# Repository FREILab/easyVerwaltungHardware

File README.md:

# easyVerwaltung Hardware

Firmware und Dokumentation für die **easyVerwaltung**-Hardware des FREILab. Das System steuert Maschinenzugang, Nutzungsprotokollierung und Sicherheit via RFID-Authentifizierung gegen das easyVerwaltung-Backend.

---

## Hardware-Übersicht

### RFID-Box — Maschinenfreigabe

| Projekt | Hardware | API | Status |
|---|---|---|---|
| [RFID_BOX_legacy](firmware/projects/RFID_BOX_legacy/) | ESP32 Dev1 | Legacy | Stabil — [v1.0.0](https://github.com/FREILab/easyVerwaltungHardware/releases/tag/rfid-box-legacy%2Fv1.0.0) |
| [RFID_BOX_easyVerwaltung](firmware/projects/RFID_BOX_easyVerwaltung/) | ESP32 Dev1 | easyVerwaltung | Getestet — Server noch nicht in Production |

### Tür-Steuerung

| Projekt | Hardware | API | Status |
|---|---|---|---|
| [DOOR_legacy](firmware/projects/DOOR_legacy/) | Arduino UNO R4 WiFi | Legacy | Scheduled for Deletion |
| [DOOR_legacy_ESPArdu](firmware/projects/DOOR_legacy_ESPArdu/) | RobotDyn UNO+WiFi R3 (ATmega328P + ESP8266) | Legacy | Stabil — [v1.0.0](https://github.com/FREILab/easyVerwaltungHardware/releases/tag/door-legacy-espardu%2Fv1.0.0) |
| [DOOR_easyVerwaltung](firmware/projects/DOOR_easyVerwaltung/) | Arduino UNO R4 WiFi | easyVerwaltung | In Entwicklung |

### Lasersaur HMI

| Projekt | Hardware | API | Status |
|---|---|---|---|
| [LASERSAUR_HMI_legacy](firmware/projects/LASERSAUR_HMI_legacy/) | Arduino Mega + Ethernet-Shield | Legacy | Stabil (nicht mit neuem Server getestet) — wird durch ESPArdu ersetzt |
| [LASERSAUR_HMI_ESPArdu](firmware/projects/LASERSAUR_HMI_ESPArdu/) | Mega2560 WiFi R3 (ATmega2560 + ESP8266) | Legacy | Implementiert, noch nicht getestet |
| [LASERSAUR_HMI_easyVerwaltung](firmware/projects/LASERSAUR_HMI_easyVerwaltung/) | Arduino Giga R1 | easyVerwaltung | In Entwicklung |

### Machine Node

| Projekt | Hardware | API | Status |
|---|---|---|---|
| [MachineNode_legacy](firmware/projects/MachineNode_legacy/) | ESP32-S3-WROOM-1-N16R8 | Legacy | Stabil |
| [MachineNode_easyVerwaltung](firmware/projects/MachineNode_easyVerwaltung/) | ESP32-S3-WROOM-1-N16R8 | easyVerwaltung | Geplant |

---

## Repository-Struktur

```
firmware/
  projects/          # Firmware-Targets (je ein PlatformIO-Projekt)
  shared/
    easyAPI/         # Gemeinsame Backend-Kommunikation (HTTP/JSON)
```

Jedes Projekt in `projects/` enthält eine eigene `README.md` mit Hardware-Details, DIP-Belegung, Flash-Anleitung und Debugging-Hinweisen.

---

## Einrichtung

### Voraussetzungen

- Python ≥ 3.8
- PlatformIO Core (`pip install platformio`)

### Credentials

Jedes Projekt benötigt eine `platformio.secrets.ini` (nicht in Git). Vorlage liegt als `.example`-Datei bei:

```bash
cp platformio.secrets.ini.example platformio.secrets.ini
# Datei befüllen, dann:
pio run
```

Details zu den Feldern stehen in der jeweiligen Projekt-README.

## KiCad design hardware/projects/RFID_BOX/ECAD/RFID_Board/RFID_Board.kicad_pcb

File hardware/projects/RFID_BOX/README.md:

# Machine Node / RFID_BOX

> **Sicherheit geht vor Kosten, Baugröße und Bauteilzahl.** Das Gerät
> schaltet Netzspannung in einer Werkstatt, in der ungeschulte Personen
> daneben stehen. Wo Ziele kollidieren, gewinnt die Sicherheit.
>
> Vier Festlegungen sind bindend und werden nicht aufgeweicht:
>
> - Die Barriere Netz ↔ SELV beträgt **8 mm Luft- und Kriechstrecke** und
>   wird nicht auf den Normwert von 5 mm reduziert. Maßgeblich sind die
>   Bauteile, die sie queren, nicht das Minimum der Norm.
> - Bauteile über der Barriere brauchen **verstärkte oder doppelte
>   Isolierung** bei 250 V Arbeitsspannung. Eine hohe Prüfspannung in kV
>   allein genügt nicht — sie sagt über die Isolationsklasse nichts aus.
> - **Ein Einzelfehler darf nicht nach außen wirken.** Neue Schaltungsteile
>   werden gegen die [FMEA](FMEA.md) geprüft, bevor sie ins Layout gehen.
> - **Beim geöffneten Gerät ist nichts Netzführendes berührbar.** Feste
>   Abdeckplatten über dem I/O-Board geben nur die Feldterminals und den
>   Sicherungshalter frei. Das RFID-Board führt kein 230 V und darf
>   angefasst werden.
>
> Breiten, Abstände und Domänen stehen in
> [Layoutregeln.md](Layoutregeln.md), die Anforderungen in
> [Anforderungen.md](Anforderungen.md). Wo das Gerät teuer ist und was eine
> Alternative kosten würde, führt [Kostenoptimierung.md](Kostenoptimierung.md)
> mit — keine der Positionen dort hebt eine der vier Festlegungen auf.

## Einleitung

Dies ist der **RFID Node**: ein kompaktes Steuergerät, das elektrische
Geräte und Maschinen in der Werkstatt (z.B. Standfräse, Drehmaschine, FKS)
per RFID-Karte freischaltet. Er prüft die Karte einer Nutzerin oder eines
Nutzers gegen easyVerwaltung, gibt bei gültiger Berechtigung die Maschine
frei und schaltet sie beim Stopp oder bei Kartenentzug wieder ab.

Technisch besteht der Node aus zwei Platinen — I/O-Board mit Netzteil und
Schaltausgang, RFID-Board mit Controller, Bedienoberfläche und
RFID-Frontend — ergänzt um optionale Erweiterungsboards für Maschinen mit
zusätzlichem Bedarf.

## Aufbau

Das Gehäuse ist 3D-gedruckt und staubdicht ausgeführt. Display und
LED-Streifen sind von aussen sichtbar und durch eine Plexiglasscheibe
geschützt; der Streifen selbst sitzt innerhalb des Gehäuses. Der Stopp-Knopf
ist von aussen erreichbar.

Das Display sitzt nicht auf der Platine, sondern in einem eigenen
3D-gedruckten Träger, der von innen hinter die Plexiglasscheibe geklippt
wird. Die Verbindung zum RFID-Board läuft über das FPC des Displays.

Die Mechanik — Gehäuse, Display-Träger, Abdeckplatten — lebt in Fusion, nicht
in diesem Repo. Von dort kommen auch die Platinenumrisse als DXF
(`PCB_outline/`).

Die beiden Platinen sitzen in verschiedenen Gehäusehälften: das
**RFID-Board am Deckel**, das **I/O-Board an der unteren Schale**. Verbunden
werden sie über ein **Kabel** — für einen Board-to-Board-Stecker ist der
Abstand zu groß. Der Deckel hängt beim Öffnen damit am Kabel.

Alle Kabel werden einseitig über Kabeldurchführungen ins Gehäuse geführt,
von links nach rechts: Netz-Eingang 230 V, Schaltausgang (geschaltete 230 V
oder Steuerleitung für ein externes Schütz), optionale Notaus-Schleife,
optionales Extension-I/O. Nicht verwendete Durchführungen werden
verschlossen.

### Berührschutz

Das Gerät wird im Servicefall geöffnet, während es unter Umständen noch am
Netz hängt. Deshalb:

- Über dem I/O-Board sitzen **fest installierte, 3D-gedruckte
  Abdeckplatten**. Sie geben nur die Feldterminals und den Sicherungshalter
  frei — beide sind berührsichere Bauformen (WAGO Hebelklemme, WR-FSH mit
  Shocksafe PC2/IP20). Alles andere Netzführende bleibt abgedeckt.
- Die Platten sind kein Deckel, der beim Öffnen mitkommt: sie bleiben am
  Board bzw. am Gehäuseunterteil und lassen sich nur mit Werkzeug lösen.
- **Das RFID-Board führt kein 230 V** und darf im geöffneten Zustand
  berührt werden. Das ist eine bindende Randbedingung — es darf kein
  netzführendes Netz auf dieses Board wandern.

Alle Boards werden **lackiert**, damit Sägemehl und Feuchtigkeit über die
Lebensdauer keine Kriechpfade bilden. Vom Lack ausgenommen bleiben
Feldterminals, Sicherungskontakte und die Steckverbinder. Der Lack
ersetzt keine Abstände: Kriech- und Luftstrecken werden bemessen, als wäre
kein Lack vorhanden.

## Elektronik

Zwei Leiterplatten, in verschiedenen Gehäusehälften:

- **RFID-Board (im Deckel):** ESP32-S3, NFC-Controller CLRC663 mit der
  RFID-Antenne, Display, LED-Streifen, Buzzer, Stopp-Taster und eine
  USB-C-Buchse für Erstprogrammierung und Debug. MCU- und RFID-Teil lagen früher getrennt
  und sind zusammengelegt.
- **I/O-Board (in der unteren Schale):** 230-V-Netz, Schaltausgang und die
  Extension-Header.
  Hiervon gibt es **zwei getrennte Boards mit eigenem Layout**, von denen
  pro Gerät genau eines bestückt wird:
  - **I/O-Board 230V** — Lastrelais und Lastmessung zum direkten Schalten
    von Lasten bis 8 A.
  - **I/O-Board 24V** — potentialfreier Kontakt für ein externes Schütz.
    Ohne Lastpfad und Lastmessung, dadurch deutlich einfacher und ohne
    Bedarf an 70 µm Kupfer.

  Beide haben denselben Formfaktor und denselben Kabelstecker zum
  RFID-Board.

Dazu kommen zwei optionale, steckbare Erweiterungsboards auf dem I/O-Board:

- **Extension Board:** generisches Zusatzboard mit zwei Bestückvarianten —
  **NAMUR** (zwei optoisolierte Ausgänge, ein galvanisch getrennter Eingang)
  oder **Digital-I/O** (noch nicht spezifiziert). Ein Node trägt höchstens
  eine Variante.
- **E-Stop Extension Board:** Relais (24 V / 100 mA), dessen Kontakt in die
  Notaus-/Interlock-Schleife oder Bremsversorgung der Maschine eingeschleift
  wird. Fail-safe: stromlos = Schleife unterbrochen. Es öffnet bei Stopp
  oder Kartenentzug sofort, während die Hauptversorgung erst nach der
  Nachlaufzeit trennt.

## Energieversorgung

Die gesamte Versorgung kommt aus dem Netz-Eingang 230 V auf dem I/O-Board
und teilt sich dort in zwei Pfade:

- **Lastpfad (nur I/O-Board 230V):** Netz-Eingang → Ausgangssicherung (F300)
  → Lastrelais (K300) → Schaltausgang. Der Shunt (R307) liegt im
  **N-Rückweg vor dem Relais**, damit die Messung unabhängig vom
  Schaltzustand betriebsbereit bleibt. K300 trennt L und N gemeinsam, weil
  die N/L-Zuordnung an der Werkstatt-Steckdose nicht garantiert eindeutig
  ist.
- **Steuerpfad:** Netz-Eingang → Sicherung F302 → Gleichtaktdrossel (L300) →
  Y-Kondensatorpaar (C305/C308, Mittelabgriff an PE) → isoliertes
  AC/DC-Modul (U300, 24 V) → Regler auf 5 V (U302). Über das Kabel geht nur
  die 5-V-Schiene zum RFID-Board; **die 3,3 V erzeugt jede Platine selbst** —
  IC304 auf dem I/O-Board für die Eingangsseite des Isolators, IC102 auf dem
  MCU-Board für ESP32, NFC-Frontend und Display. Der DC-DC im Isolator zieht
  seinen Strom damit lokal und nicht über 30 cm Kabel. Die 24-V-Schiene
  versorgt die Relaisspule und bleibt auf dem I/O-Board; zum MCU-Board geht
  statt der Schiene nur ein Teilersignal zur Überwachung. LED-Leiste und
  Buzzer laufen direkt auf 5 V.
- **USB-C:** Das RFID-Board lässt sich auch allein über USB versorgen. VBUS
  (D401) und die 5 V vom Kabel (D100) laufen über je eine Schottky-Diode SS14
  auf +5V; keine Quelle speist in die andere zurück. Die Schiene liegt damit
  rund 0,4 V unter 5 V — für den 74AHCT125 (min. 4,5 V) knapp ausreichend.

Die **Lastmessung** liegt auf Netzpotential. Versorgung und UART laufen über
den Digitalisolator U301 (ISOW7721) mit integriertem DC-DC-Wandler, gespeist
aus der SELV-Seite — die Insel führt keinen eigenen Netzzweig. Über `ISO_EN`
nimmt die Firmware der Insel die Versorgung und startet das Mess-IC U303 neu.

Die Erweiterungsboards stecken auf dem I/O-Board und werden aus dem
Steuerpfad versorgt;
ihre Feldseite bleibt galvanisch getrennt und wird extern gespeist.

PE wird unverändert vom Netz-Eingang zum Schaltausgang durchgeschleift und
trägt den Mittelabgriff von C305/C308. Das Gehäuse ist Kunststoff, es gibt
keine Gehäusemasse.

**Sicherungen.** Die Lastausgangssicherung (F300) ist gesockelt und nach dem
Öffnen des Gehäuses ohne Löten tauschbar; eine Ersatzsicherung wird im
Gehäuse mitgeführt. Die Gerätesicherung (F302) ist als dokumentierte
Ausnahme fest verlötet (siehe [Anforderungen.md](Anforderungen.md), S5). Vor
F302 liegt R303, ein Sicherungswiderstand mit 10 Ω, der den Kurzschlussstrom
im Steuerzweig auf rund 25 A begrenzt — unter das Ausschaltvermögen von 35 A
der MRT.

**EMV.** Am Netz-Eingang liegen RV300 als Überspannungsschutz und C300 als
X2-Kondensator; eine Entladekette aus drei Widerständen bringt die
Steckerstifte in 0,17 s unter 60 V. Das Gleichtaktfilter aus L300 und
C305/C308 sitzt im Steuerzweig direkt vor U300, also an der Störquelle;
der Lastpfad trägt kein Filterbauteil. Auslegungspunkt ist 150 kHz bei 20 dB
Dämpfung. Drei Grenzen gelten dabei:

- Der Mittelabgriff nach PE ist zwingend — ohne ihn hat der Gleichtaktstrom
  im Kunststoffgehäuse keinen Rückweg, und die Drossel wirkt nur noch über
  ihre Streuinduktivität.
- Cy ist nach oben durch den Ableitstrom begrenzt; mehrere Nodes hängen am
  selben FI-Kreis.
- L nominal im Fenster 3–10 mH: nach unten setzt die Eckfrequenz die Grenze,
  nach oben die Eigenresonanz der Drossel.

**Bewusst nicht vorhanden:** eine Kontakt-Schutzbeschaltung am Lastrelais —
der Node ist Lastschalter, das Entkoppeln der Lastgeräte vom Netz ist nicht
seine Aufgabe. Und eine Einschaltstrombegrenzung im Lastpfad — den Anlauf
tragen die träge Ausgangssicherung und das Einschaltvermögen von K300
(30 A, AgCdO-Kontakte).

## Signalfluss

Der Signalfluss beginnt an der RFID-Karte und endet am Schaltausgang. Vier
Aussagen, die man kennen muss:

- Der Stopp-Taster wirkt **nur über die Firmware** auf den ESP32. Einen
  hardwareseitigen Bypass gibt es nicht, weder am E-Stop-Relais noch am
  Relaistreiber der Hauptversorgung.
- Das Enable bleibt vollständig auf der SELV-Seite. Die Relaisspule hängt an
  der isolierten 24-V-Schiene und wird von **zwei Schaltern in Reihe**
  geführt: Low-Side-NMOS (Q301) und High-Side-PMOS (Q300) an getrennten
  GPIOs. Beide gehen im Ruhezustand sicher auf, und ein durchlegierter
  Schalter lässt sich über den anderen noch abschalten.
- Die Hauptversorgung wird ausschliesslich vom ESP32 nach Ablauf der
  Nachlaufzeit abgeschaltet; das E-Stop-Relais öffnet sofort.
- Die Isolationsbarriere quert nur die UART der Lastmessung, über U301 — er
  führt zugleich die Versorgung der Insel hinüber.

```mermaid
flowchart TB
    Antenne([RFID-Antenne])
    NFC["NFC-Controller CLRC663<br/>[3V3]"]
    ESP["ESP32<br/>[3V3]"]
    STOP["Stopp-Taster<br/>[3V3]"]
    TREIBER["Relaistreiber<br/>Low-Side NMOS + High-Side PMOS<br/>Gate [3V3] / Spule [24V]"]
    REL["Lastrelais<br/>Spule [24V] / Kontakt [230V]"]
    OUT([Terminal: Schaltausgang])

    MESS["Lastmessung<br/>Steuerseite<br/>Signal [3V3_ISO], netzbezogen"]
    OPTO_FB["Digitalisolator<br/>UART und Versorgung der Insel"]

    EXT["Extension Board<br/>[5V]"]
    ESTOP["E-Stop Relais<br/>[5V]"]
    OLED["OLED (ggf.)<br/>[3V3]"]

    Antenne -->|RF-Feld| NFC
    NFC -->|SPI| ESP
    ESP -->|Enable| TREIBER
    TREIBER -->|Ansteuerung| REL
    REL --> OUT

    STOP -->|I/O| ESP

    MESS <-->|UART| OPTO_FB
    OPTO_FB <-->|UART, isoliert| ESP

    ESP -->|I/O| EXT
    ESP -->|Enable| ESTOP
    ESP -->|I2C| OLED

    classDef term230 fill:#1565c0,color:#fff,stroke:#0d47a1
    classDef part230 fill:#ff9800,color:#000,stroke:#e65100
    classDef partSELV fill:#81c784,color:#000,stroke:#2e7d32
    classDef iso fill:#fff,color:#000,stroke:#6a1b9a,stroke-width:3px
    classDef touch230 fill:#fdd835,color:#000,stroke:#f57f17

    class OUT term230
    class REL part230
    class Antenne,NFC,ESP,STOP,EXT,ESTOP,OLED,TREIBER partSELV
    class MESS touch230
    class OPTO_FB iso
```

Abgerundet = Terminal oder Eingabe, eckig = Funktionsblock. Grün =
Kleinspannung, orange = 230-V-führend, blau = 230-V-Terminal, gelb =
Signalpegel isoliert, Bauteil berührt aber die Netzseite, weiss mit
violettem Rahmen = Isolationsbarriere. `[…]` nennt den Signalpegel.

## Kernbauteile

Nur die Teile, die das Gerät bestimmen. Dazu die Sicherung: **im Servicefall
wird nur sie getauscht**, alles andere ist fest verlötet. Denkbar wäre noch
das Display, das über sein FPC steckbar ist.

Die vollständige Liste steht im Schaltplan und in
`ECAD/IO_Board/IO_Board.csv`, die Preise in `MyCSLib/KiCad/parts_db.json`.

| Funktion | Hersteller / Teilenummer | Warum dieser |
|---|---|---|
| Mikrocontroller | Espressif<br>ESP32-S3-WROOM-1-N16R8 | WLAN/BLE, 16 MB Flash, 8 MB PSRAM |
| Lastrelais (K300) | TE Connectivity<br>T92S11D12-24 | 2-polig (N+L), 30 A Einschaltvermögen, verstärkte Isolation Spule/Kontakt 8 mm / 9,5 mm / 4 kVrms. Bauhöhe 30,7 mm |
| Potentialfreier Kontakt, E-Stop (K2, K3) | Omron<br>G5V-1-2 DC24 | 100 mA / 24 V, Spule 24 V |
| Display | EastRising<br>ER-TFT020-3 | 2" IPS, 240×320, 4-Wire SPI. Ersetzt das DT010ATFT bei gleichem Bustyp, 5,3-fache aktive Fläche. Nacktes Panel, Anschluss über steckbares FPC 14-pol / 0,5 mm |
| Lastausgangssicherung + Ersatz (F300) | Bel Fuse<br>5HT 10-R | 10 A / 250 V träge, Keramik sandgefüllt, **Ausschaltvermögen 1500 A**. Die Glasrohrtype mit 100 A reicht nicht. Die VDE-Lizenz der Baureihe deckt nur 1–6,3 A, die 10 A laufen über UL, CSA und CCC |
| Gerätesicherung (F302) | Bel Fuse<br>MRT 500-BULK | 500 mA / 250 V träge, IEC 60127-3. Fest verlötet, dokumentierte Ausnahme zu S5 |

## TODO

- RV300 liegt vor F300 und F302 und ist damit ungesichert. Ein Varistor am
  Lebensdauerende versagt niederohmig; vorgelagert wirkt nur der
  Leitungsschutzschalter im Werkstattverteiler. Thermisch geschützten
  Varistor (ThermoFuse) prüfen.
- **Auftrennbare Netzbrücken** an ausgewählten Stellen der Niederspannung
  vorsehen, damit sich Zweige zur Inbetriebnahme einzeln zuschalten lassen.
- **Testpunkte** für die Inbetriebnahme vorsehen. In der Netzdomäne und auf
  der ISO-Insel nur berührgeschützt zugänglich (U8, U9).
- Die Netzklassen im KiCad-Projekt tragen noch keine Breiten und Abstände;
  eine Klasse `3V3` fehlt, `+3V3` hängt derzeit in `Signals`.
- **Isolator U301 entscheiden.** Der ISOW7721DFMR ist bei Mouser und
  Digi-Key auf null, Status trotzdem „Aktiv". Lagernd ist nur der
  ISOW7721**F**DFMR, dessen Ausgänge bei stromloser Eingangsseite auf LOW
  statt HIGH gehen. Da `ISO_EN` die Insel im Betrieb abschaltet, sähe die
  UART des ESP32 dann dauerhaft Break — die Firmware müsste den Empfänger
  abschalten, solange die Insel aus ist. Entweder das, oder den D-Typ
  vorbestellen.
- **Verbindungskabel (FFC, J102 ↔ J302):** Dummy-Bauteil für das Kabel GCT
  `10-14-x-xxxx-C-4-08-4-T` anlegen; Länge und Kontaktseite (Typ A/D) in
  Fusion bestimmen. Pads 15/16 (Lötlaschen) des SFW14S haben keinen Pin im
  Symbol.

### Offen aus der Bauteilplanung

- **Piezo PKLCS1212E40A1-R1 ist bei Digi-Key Last Time Buy** (Mouser 27.236
  Stück). Alternative mit aktivem Status wäre `CMT-1203-SMT-TR` von Same
  Sky — dafür ohne fertiges KiCad-Footprint und 3 dB leiser.
- **Quarz Y200:** das Symbol hat zwei Pins, das Footprint vier Pads. Die
  beiden Gehäusepads bleiben ohne Netz. Sollen sie auf GND, muss der Master
  von `Device:Crystal_GND24` kommen.
- **I/O-Board 24V zeichnen:** zwei potentialfreie Kontakte für externes
  Hauptschütz und Aux-Ausgang. Die Kontakte müssen den Einschaltstrom einer
  Schützspule tragen — ein Signalrelais wie das G5V-1 reicht dafür nicht.
  Der Haupt-Kontakt braucht dieselbe Verriegelung aus zwei Schaltern wie
  K300, für Aux genügt ein Low-Side-Schalter.
- **`aux_en` und `EXT_IO`** auf dem I/O-Board beschalten (E-Stop- bzw.
  Extension-Header); sie enden derzeit an J302.
- **Stopp-Taster auswählen** (Panel-Mount im Gehäuse, angeschlossen an J101).
- **`antenna/README.md` nachziehen:** dort stehen C₀ mit 50 V und
  R<sub>S</sub> mit 2,4 Ω im 0603, bestückt sind 100 V und 2,49 Ω im 1206.
- **Anforderung A1 nachziehen:** aus dem LED-Ring mit zwölf LEDs ist eine
  Leiste über dem Display mit **sieben** LEDs geworden, dazu kommt die
  Statusliste.

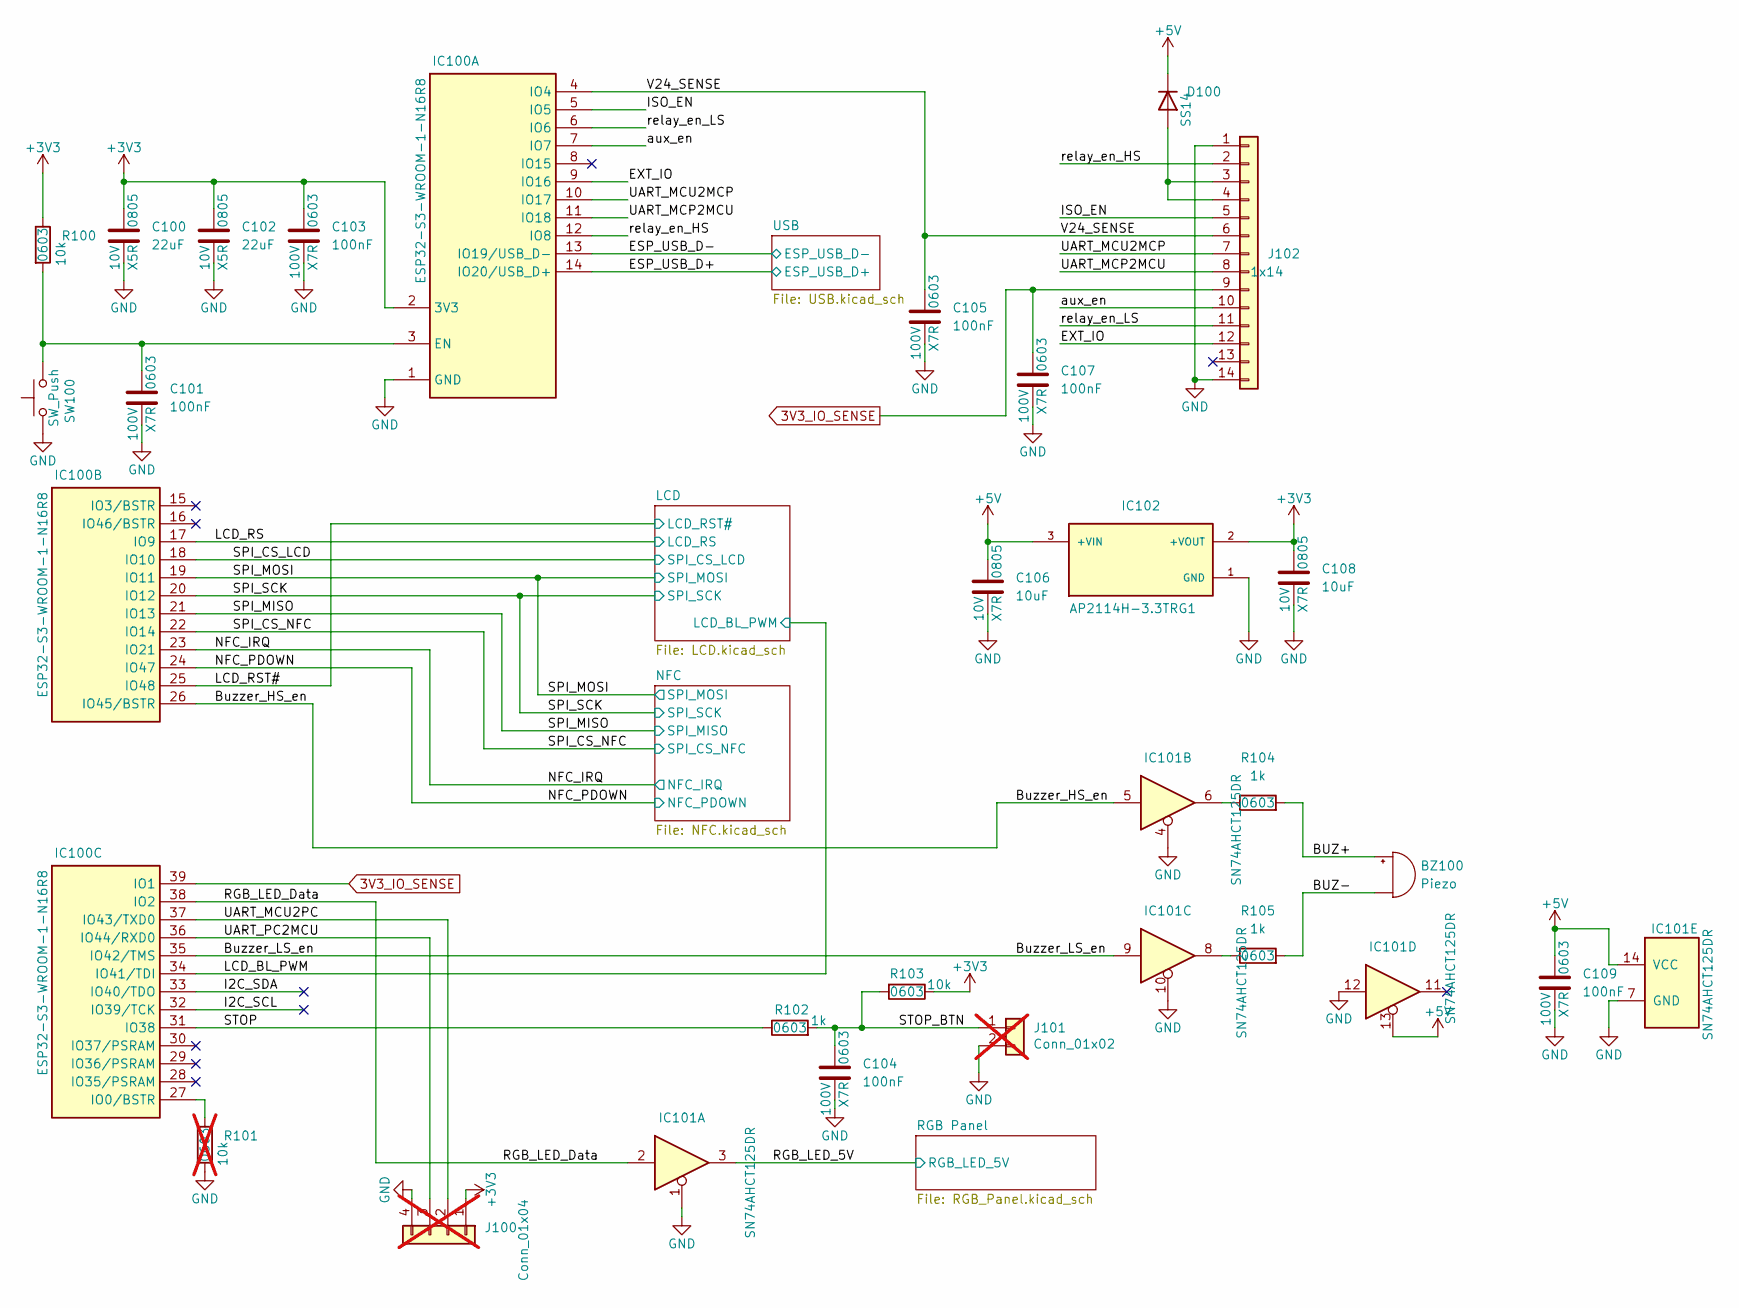
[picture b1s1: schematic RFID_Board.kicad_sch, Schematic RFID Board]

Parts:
BZ100: Piezo; Buzzer_Murata_PKLCS1212E; Manufacturer Part Number PKLCS1212E40A1-R1
C100, C102: 22uF; C_0805_2012Metric; Voltage Rating 10V; Manufacturer Part Number GRM21BR61A226ME51K
C101, C103, C104, C105, C107, C109: 100nF; C_0603_1608Metric; Voltage Rating 100V; Manufacturer Part Number 885012206120
C106, C108: 10uF; C_0805_2012Metric; Voltage Rating 10V; Manufacturer Part Number CC0805KFX7R6BB106
D100: SS14; D_SMA; Manufacturer Part Number SS14
IC100: ESP32-S3-WROOM-1-N16R8; IC_ESP32S3WROOM1N16R8; Manufacturer Part Number ESP32-S3-WROOM-1-N16R8
IC101: SN74AHCT125DR; SOIC-14_3.9x8.7mm_P1.27mm; Manufacturer Part Number SN74AHCT125DR
IC102: AP2114H-3.3TRG1; SOT-223-3_TabPin2; Manufacturer Part Number AP2114H-3.3TRG1
J100: Conn_01x04; not fitted
J101: Conn_01x02; not fitted
J102: 1x14; J_01x14_SFW14S-2STE1LF; Manufacturer Part Number SFW14S-2STE1LF
R100, R103: 10k; R_0603_1608Metric; Tolerance 1%; Manufacturer Part Number CRCW060310K0FKEAC
R101: 10k; R_0603_1608Metric; Tolerance 1%; Manufacturer Part Number CRCW060310K0FKEAC; not fitted
R102, R104, R105: 1k; R_0603_1608Metric; Tolerance 1%; Manufacturer Part Number CRCW06031K00FKEAC
SW100: SW_Push; SW_SPST_TL3305A; Manufacturer Part Number TL3305AF160QG

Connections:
3V3_IO_SENSE: C107.1, IC100.39 (IO1), J102.9
+3V3: C100.1, C102.1, C103.1, C108.1, IC100.2 (3V3), IC102.2 (+VOUT), J100.1, R100.1, R103.1; also elsewhere on the board
+5V: C106.1, C109.1, D100.1 (K), IC101.13, IC101.14 (VCC), IC102.3 (+VIN); also elsewhere on the board
/BUZ+: BZ100.1 (+), R104.2
/BUZ-: BZ100.2 (-), R105.2
/Buzzer_HS_en: IC100.26 (IO45/BSTR), IC101.5
/Buzzer_LS_en: IC100.35 (IO42/TMS), IC101.9
/ESP_USB_D+: IC100.14 (IO20/USB_D+); also elsewhere on the board
/ESP_USB_D-: IC100.13 (IO19/USB_D-); also elsewhere on the board
/EXT_IO: IC100.9 (IO16), J102.12
/I2C_SCL: IC100.32 (IO39/TCK)
/I2C_SDA: IC100.33 (IO40/TDO)
/ISO_EN: IC100.5 (IO5), J102.5
/LCD_BL_PWM: IC100.34 (IO41/TDI); also elsewhere on the board
/LCD_RS: IC100.17 (IO9); also elsewhere on the board
/LCD_RST#: IC100.25 (IO48); also elsewhere on the board
/NFC_IRQ: IC100.23 (IO21); also elsewhere on the board
/NFC_PDOWN: IC100.24 (IO47); also elsewhere on the board
/RGB_LED_5V: IC101.3; also elsewhere on the board
/RGB_LED_Data: IC100.38 (IO2), IC101.2
/SPI_CS_LCD: IC100.18 (IO10); also elsewhere on the board
/SPI_CS_NFC: IC100.22 (IO14); also elsewhere on the board
/SPI_MISO: IC100.21 (IO13); also elsewhere on the board
/SPI_MOSI: IC100.19 (IO11); also elsewhere on the board
/SPI_SCK: IC100.20 (IO12); also elsewhere on the board
/STOP: IC100.31 (IO38), R102.1
/STOP_BTN: C104.1, J101.1, R102.2, R103.2
/UART_MCP2MCU: IC100.11 (IO18), J102.8
/UART_MCU2MCP: IC100.10 (IO17), J102.7
/UART_MCU2PC: IC100.37 (IO43/TXD0), J100.2
/UART_PC2MCU: IC100.36 (IO44/RXD0), J100.3
/V24_SENSE: C105.1, IC100.4 (IO4), J102.6
/aux_en: IC100.7 (IO7), J102.10
/relay_en_HS: IC100.12 (IO8), J102.2
/relay_en_LS: IC100.6 (IO6), J102.11
GND: C100.2, C101.2, C102.2, C103.2, C104.2, C105.2, C106.2, C107.2, C108.2, C109.2, IC100.1 (GND), IC100.40 (GND), IC100.41 (GND), IC100.42 (GND), IC100.43 (GND), IC100.44 (GND), IC100.45 (GND), IC100.46 (GND), IC100.47 (GND), IC100.48 (GND), IC100.49 (GND), IC101.1, IC101.4, IC101.7 (GND), IC101.10, IC101.12, IC102.1 (GND), J100.4, J101.2, J102.1, J102.14, R101.2, SW100.1; also elsewhere on the board
unnamed: D100.2 (A), J102.3, J102.4
unnamed: C101.1, IC100.3 (EN), R100.2, SW100.2
unnamed: IC100.27 (IO0/BSTR), R101.1
unnamed: IC101.6, R104.1
unnamed: IC101.8, R105.1

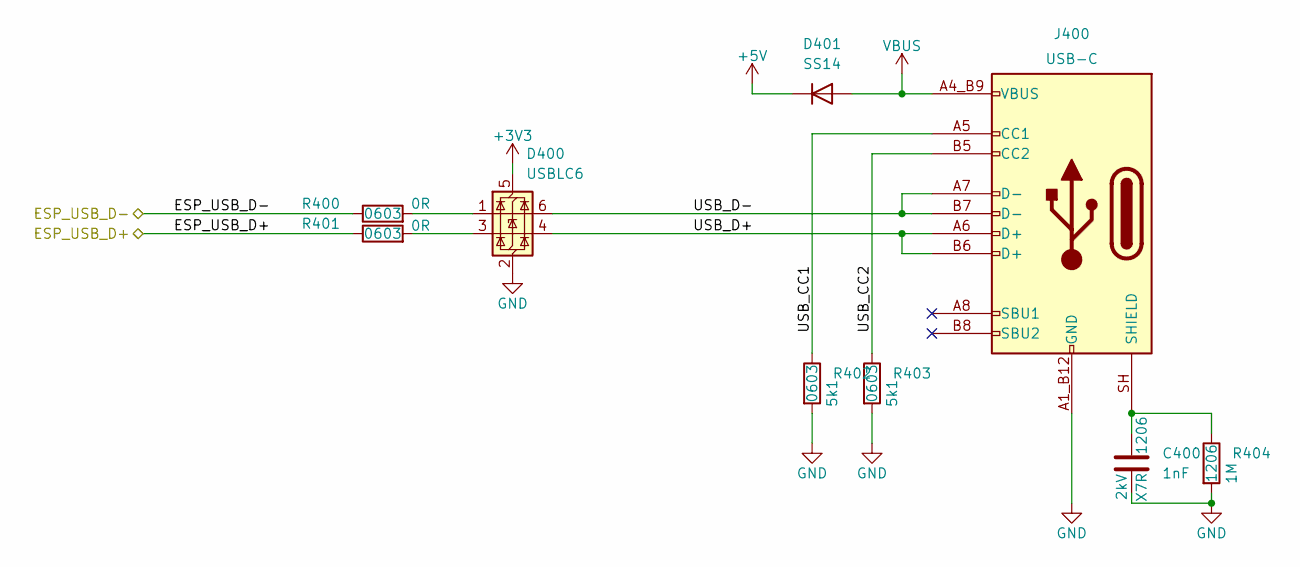
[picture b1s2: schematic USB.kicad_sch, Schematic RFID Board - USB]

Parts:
C400: 1nF; C_1206_3216Metric; Voltage Rating 2kV; Manufacturer Part Number 885342208024
D400: USBLC6; SOT-23-6; Manufacturer Part Number USBLC6-2SC6Y
D401: SS14; D_SMA; Manufacturer Part Number SS14
J400: USB-C; J_USB-C_USB4105-GF-A; Manufacturer Part Number USB4105-GF-A
R400, R401: 0R; R_0603_1608Metric; Tolerance 1%; Manufacturer Part Number CRCW06030000Z0EBC
R402, R403: 5k1; R_0603_1608Metric; Tolerance 1%; Manufacturer Part Number CRCW06035K10FKEA
R404: 1M; R_1206_3216Metric; Tolerance 1%; Manufacturer Part Number CRCW12061M00FKEA

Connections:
+3V3: D400.5 (VBUS); also elsewhere on the board
+5V: D401.1 (K); also elsewhere on the board
/ESP_USB_D+: R401.1; also elsewhere on the board
/ESP_USB_D-: R400.1; also elsewhere on the board
/USB/USB_CC1: J400.A5 (CC1), R402.1
/USB/USB_CC2: J400.B5 (CC2), R403.1
/USB/USB_D+: D400.4 (I/O2), J400.A6 (D+), J400.B6 (D+)
/USB/USB_D-: D400.6 (I/O1), J400.A7 (D-), J400.B7 (D-)
GND: C400.2, D400.2 (GND), J400.A1_B12 (GND), J400.B1_A12 (GND), R402.2, R403.2, R404.2; also elsewhere on the board
unnamed: D400.1 (I/O1), R400.2
unnamed: D400.3 (I/O2), R401.2
unnamed: C400.1, J400.SH (SHIELD), R404.1
VBUS: D401.2 (A), J400.A4_B9 (VBUS), J400.B4_A9 (VBUS)

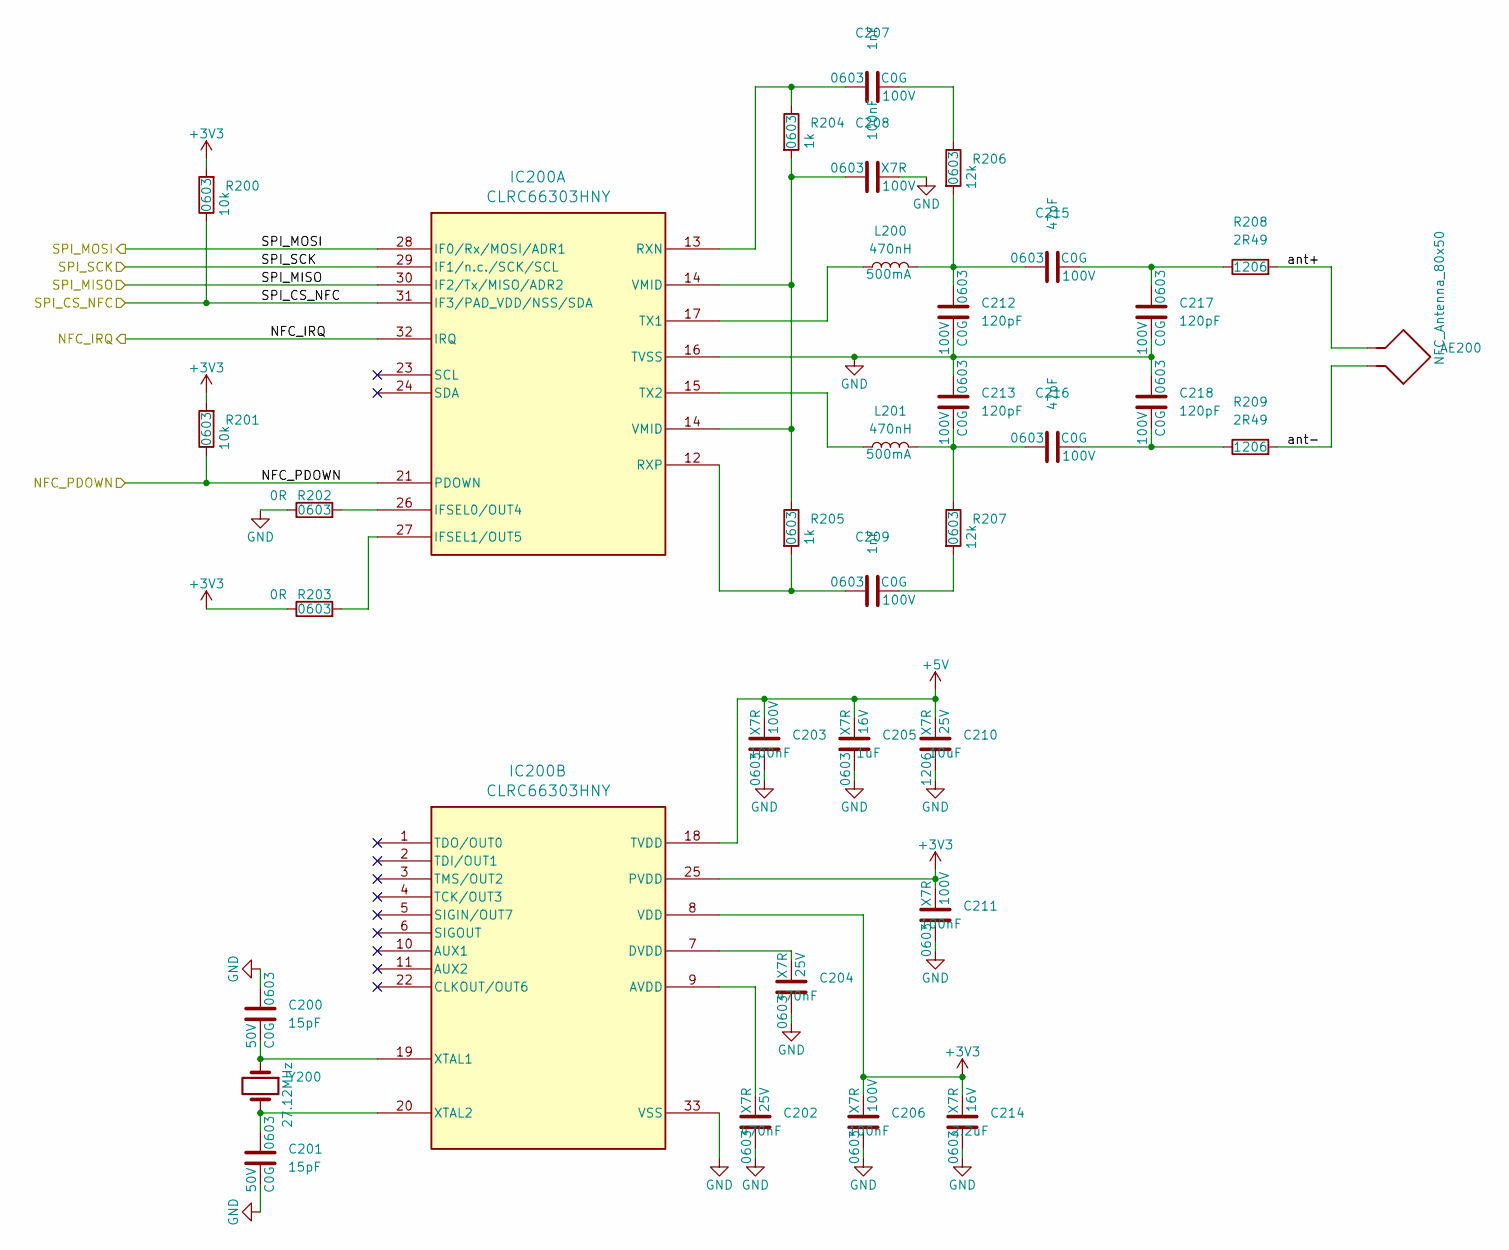
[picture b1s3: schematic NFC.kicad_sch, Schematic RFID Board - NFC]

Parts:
AE200: NFC_Antenna_80x50; NFC_Loop_80x50_5T
C200, C201: 15pF; C_0603_1608Metric; Voltage Rating 50V; Manufacturer Part Number 885012006052
C202, C204: 470nF; C_0603_1608Metric; Voltage Rating 25V; Manufacturer Part Number GRM188R71E474KA12D
C203, C206, C208, C211: 100nF; C_0603_1608Metric; Voltage Rating 100V; Manufacturer Part Number 885012206120
C205: 1uF; C_0603_1608Metric; Voltage Rating 16V; Manufacturer Part Number CGA3E1X7R1C105K080AC
C207, C209: 1nF; C_0603_1608Metric; Voltage Rating 100V; Manufacturer Part Number GCM1885C2A102JA16D
C210: 10uF; C_1206_3216Metric; Voltage Rating 25V; Manufacturer Part Number GRM31CR71E106KA12L
C212, C213, C217, C218: 120pF; C_0603_1608Metric; Voltage Rating 100V; Manufacturer Part Number GCM1885C2A121FA16J
C214: 2.2uF; C_0603_1608Metric; Voltage Rating 16V; Manufacturer Part Number GRM188Z71C225KE43J
C215, C216: 47pF; C_0603_1608Metric; Voltage Rating 100V; Manufacturer Part Number GCM1885C2A470FA16D
IC200: CLRC66303HNY; HVQFN-32-1EP_5x5mm_P0.5mm_EP3.1x3.1mm; Manufacturer Part Number CLRC66303HNY
L200, L201: 470nH; L_0603_1608Metric; Manufacturer Part Number LQW18CNR47J0HD
R200, R201: 10k; R_0603_1608Metric; Tolerance 1%; Manufacturer Part Number CRCW060310K0FKEAC
R202, R203: 0R; R_0603_1608Metric; Tolerance 1%; Manufacturer Part Number CRCW06030000Z0EBC
R204, R205: 1k; R_0603_1608Metric; Tolerance 1%; Manufacturer Part Number CRCW06031K00FKEAC
R206, R207: 12k; R_0603_1608Metric; Tolerance 1%; Manufacturer Part Number CRCW060312K0FKEAC
R208, R209: 2R49; R_1206_3216Metric; Tolerance 1%; Manufacturer Part Number CRCW12062R49FKEA
Y200: 27.12MHz; Y_XRCGB; Manufacturer Part Number XRCGB27M120F3M10R0

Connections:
+3V3: C206.2, C211.2, C214.2, IC200.8 (VDD), IC200.25 (PVDD), R200.2, R201.2, R203.1; also elsewhere on the board
+5V: C203.2, C205.2, C210.2, IC200.18 (TVDD); also elsewhere on the board
/NFC/ant+: AE200.1, R208.2
/NFC/ant-: AE200.2, R209.2
/NFC_IRQ: IC200.32 (IRQ); also elsewhere on the board
/NFC_PDOWN: IC200.21 (PDOWN), R201.1; also elsewhere on the board
/SPI_CS_NFC: IC200.31 (IF3/PAD_VDD/NSS/SDA), R200.1; also elsewhere on the board
/SPI_MISO: IC200.30 (IF2/Tx/MISO/ADR2); also elsewhere on the board
/SPI_MOSI: IC200.28 (IF0/Rx/MOSI/ADR1); also elsewhere on the board
/SPI_SCK: IC200.29 (IF1/n.c./SCK/SCL); also elsewhere on the board
GND: C200.1, C201.2, C202.1, C203.1, C204.1, C205.1, C206.1, C208.2, C210.1, C211.1, C212.2, C213.1, C214.1, C217.2, C218.1, IC200.16 (TVSS), IC200.33 (VSS), R202.1; also elsewhere on the board
unnamed: C207.2, R206.1
unnamed: C209.2, R207.2
unnamed: C212.1, C215.1, L200.2, R206.2
unnamed: C213.2, C216.1, L201.2, R207.1
unnamed: C215.2, C217.1, R208.1
unnamed: C216.2, C218.2, R209.1
unnamed: IC200.26 (IFSEL0/OUT4), R202.2
unnamed: IC200.27 (IFSEL1/OUT5), R203.2
unnamed: C207.1, IC200.13 (RXN), R204.1
unnamed: C209.1, IC200.12 (RXP), R205.2
unnamed: IC200.17 (TX1), L200.1
unnamed: IC200.15 (TX2), L201.1
unnamed: C208.1, IC200.14 (VMID), R204.2, R205.1
unnamed: C202.2, IC200.9 (AVDD)
unnamed: C204.2, IC200.7 (DVDD)
unnamed: C200.2, IC200.19 (XTAL1), Y200.1
unnamed: C201.1, IC200.20 (XTAL2), Y200.3
unnamed: Y200.2, Y200.4

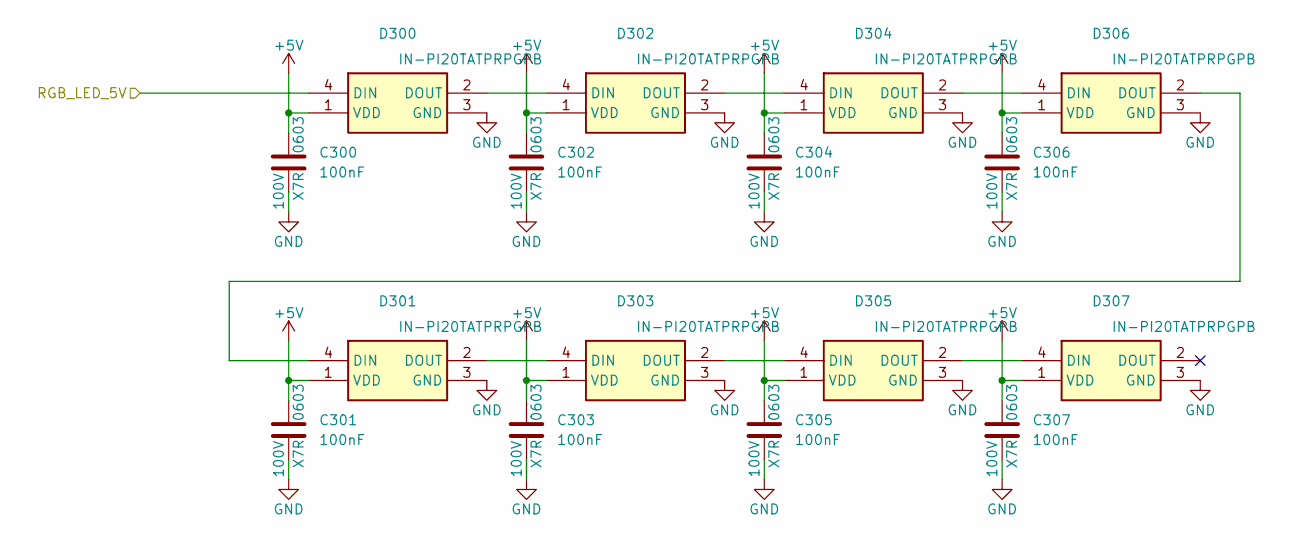
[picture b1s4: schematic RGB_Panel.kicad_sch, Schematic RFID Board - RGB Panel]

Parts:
C300, C301, C302, C303, C304, C305, C306, C307: 100nF; C_0603_1608Metric; Voltage Rating 100V; Manufacturer Part Number 885012206120
D300, D301, D302, D303, D304, D305, D306, D307: IN-PI20TATPRPGPB; LED_INPI20TATPRPGPB; Manufacturer Part Number IN-PI20TATPRPGPB

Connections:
+5V: C300.1, C301.1, C302.1, C303.1, C304.1, C305.1, C306.1, C307.1, D300.1 (VDD), D301.1 (VDD), D302.1 (VDD), D303.1 (VDD), D304.1 (VDD), D305.1 (VDD), D306.1 (VDD), D307.1 (VDD); also elsewhere on the board
/RGB_LED_5V: D300.4 (DIN); also elsewhere on the board
GND: C300.2, C301.2, C302.2, C303.2, C304.2, C305.2, C306.2, C307.2, D300.3 (GND), D301.3 (GND), D302.3 (GND), D303.3 (GND), D304.3 (GND), D305.3 (GND), D306.3 (GND), D307.3 (GND); also elsewhere on the board
unnamed: D300.2 (DOUT), D302.4 (DIN)
unnamed: D301.4 (DIN), D306.2 (DOUT)
unnamed: D301.2 (DOUT), D303.4 (DIN)
unnamed: D302.2 (DOUT), D304.4 (DIN)
unnamed: D303.2 (DOUT), D305.4 (DIN)
unnamed: D304.2 (DOUT), D306.4 (DIN)
unnamed: D305.2 (DOUT), D307.4 (DIN)

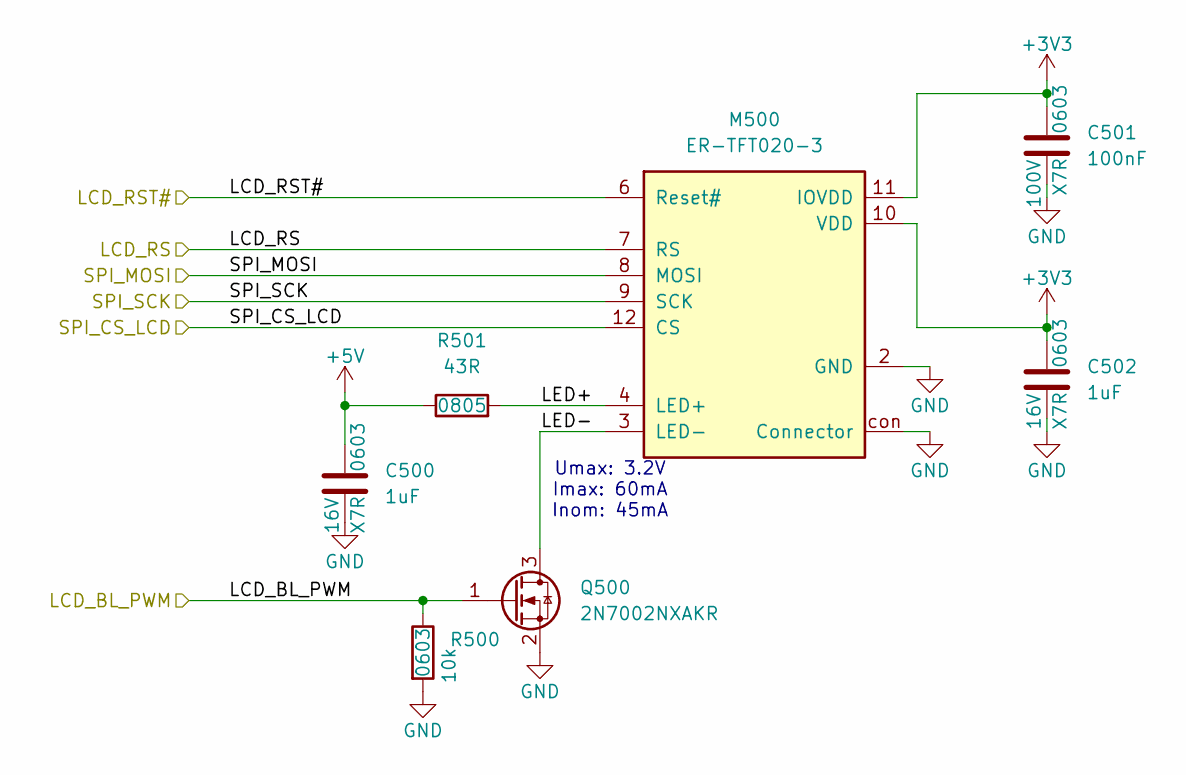
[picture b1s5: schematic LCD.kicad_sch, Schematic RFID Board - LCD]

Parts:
C500, C502: 1uF; C_0603_1608Metric; Voltage Rating 16V; Manufacturer Part Number CGA3E1X7R1C105K080AC
C501: 100nF; C_0603_1608Metric; Voltage Rating 100V; Manufacturer Part Number 885012206120
M500: ER-TFT020-3; LCD_ER-TFT020-3; Manufacturer Part Number FH12-14S-0.5SH(55)
Q500: 2N7002NXAKR; SOT-23; Manufacturer Part Number 2N7002NXAKR
R500: 10k; R_0603_1608Metric; Tolerance 1%; Manufacturer Part Number CRCW060310K0FKEAC
R501: 43R; R_0805_2012Metric; Tolerance 1%; Manufacturer Part Number CRCW080543R0FKEA

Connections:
+3V3: C501.1, C502.1, M500.10 (VDD), M500.11 (IOVDD); also elsewhere on the board
+5V: C500.1, R501.1; also elsewhere on the board
/LCD/LED+: M500.4 (LED+), R501.2
/LCD/LED-: M500.3 (LED-), Q500.3 (D)
/LCD_BL_PWM: Q500.1 (G), R500.1; also elsewhere on the board
/LCD_RS: M500.7 (RS); also elsewhere on the board
/LCD_RST#: M500.6 (Reset#); also elsewhere on the board
/SPI_CS_LCD: M500.12 (CS); also elsewhere on the board
/SPI_MOSI: M500.8 (MOSI); also elsewhere on the board
/SPI_SCK: M500.9 (SCK); also elsewhere on the board
GND: C500.2, C501.2, C502.2, M500.2 (GND), M500.5 (GND), M500.13 (GND), M500.con (Connector), Q500.2 (S), R500.2; also elsewhere on the board

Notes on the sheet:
Umax: 3.2V Imax: 60mA Inom: 45mA

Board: 2 copper layers, 91 parts (17 on the bottom side), 76 nets, no tracks yet.
